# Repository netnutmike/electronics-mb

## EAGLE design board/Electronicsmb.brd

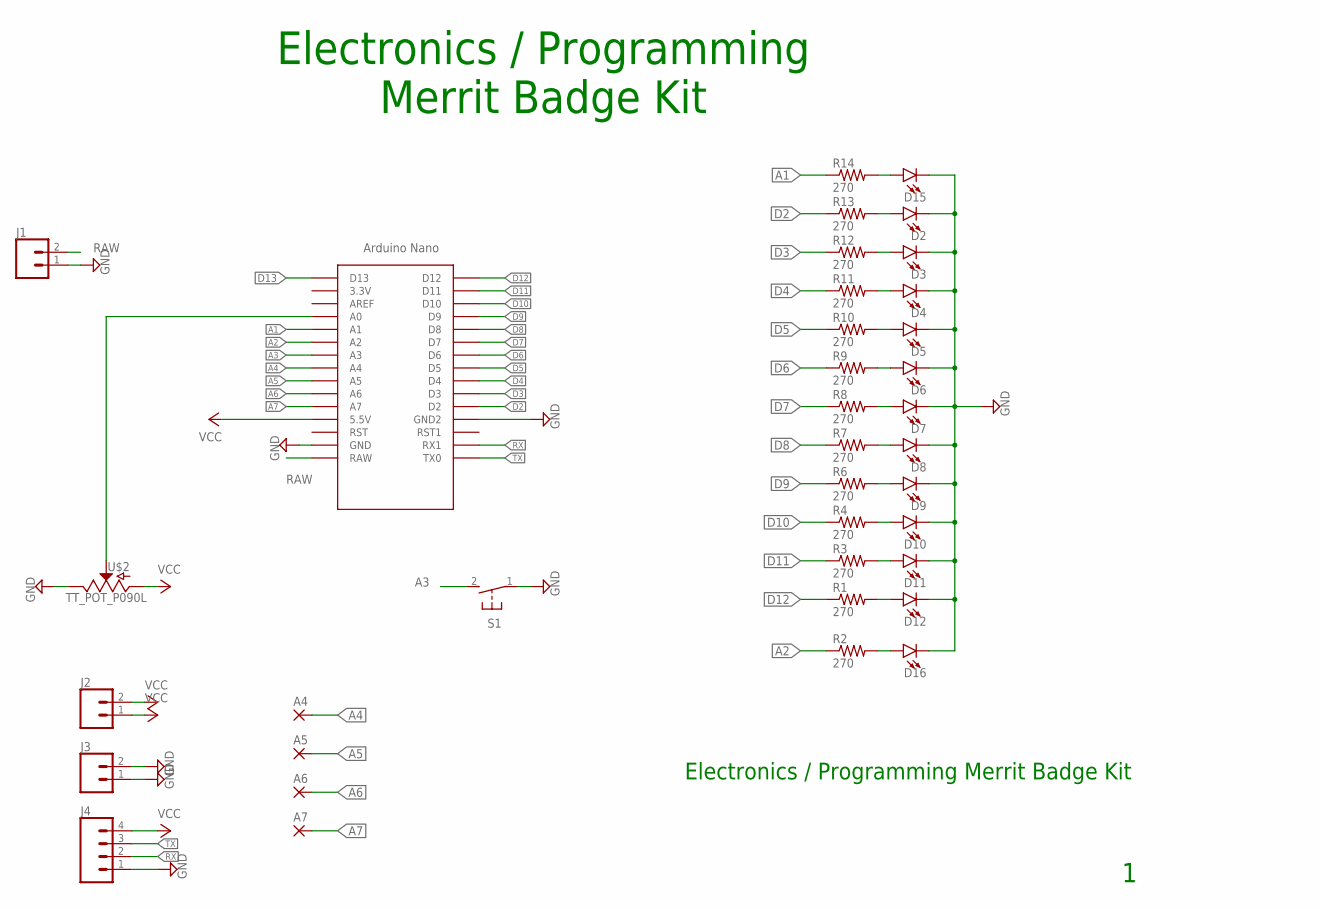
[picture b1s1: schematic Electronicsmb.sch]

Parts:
A4, A5, A6, A7: 2,54/1,0
D2, D3, D4, D5, D6, D7, D8, D9, D10, D11, D12, D15, D16: LED5MM; LED_5MM
J1, J2, J3: CONN_02; 1X02
J4: CONN_04; 1X04
R1, R2, R3, R4, R6, R7, R8, R9, R10, R11, R12, R13, R14: 270; AXIAL-0.4
S1: 31-XX; B3F-31XX
U$1: NANO
U$2: TT_POT_P090L; TT_POT

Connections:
A1: R14.P$1 (1), U$1.A1
A2: R2.P$1 (1), U$1.A2
A3: S1.2 (S), U$1.A3
A4: A4.1, U$1.A4
A5: A5.1, U$1.A5
A6: A6.1, U$1.A6
A7: A7.1, U$1.A7
D2: R13.P$1 (1), U$1.D2
D3: R12.P$1 (1), U$1.D3
D4: R11.P$1 (1), U$1.D4
D5: R10.P$1 (1), U$1.D5
D6: R9.P$1 (1), U$1.D6
D7: R8.P$1 (1), U$1.D7
D8: R7.P$1 (1), U$1.D8
D9: R6.P$1 (1), U$1.D9
D10: R4.P$1 (1), U$1.D10
D11: R3.P$1 (1), U$1.D11
D12: R1.P$1 (1), U$1.D12
D13: U$1.D13
GND: D2.K (C), D3.K (C), D4.K (C), D5.K (C), D6.K (C), D7.K (C), D8.K (C), D9.K (C), D10.K (C), D11.K (C), D12.K (C), D15.K (C), D16.K (C), J1.1, J3.1, J3.2, J4.1, S1.1, U$1.GND, U$1.GND1 (GND2), U$2.P$3 (E)
unnamed: D16.A, R2.P$2 (2)
unnamed: D15.A, R14.P$2 (2)
unnamed: D2.A, R13.P$2 (2)
unnamed: D3.A, R12.P$2 (2)
unnamed: D4.A, R11.P$2 (2)
unnamed: D5.A, R10.P$2 (2)
unnamed: D6.A, R9.P$2 (2)
unnamed: D7.A, R8.P$2 (2)
unnamed: D8.A, R7.P$2 (2)
unnamed: D9.A, R6.P$2 (2)
unnamed: D10.A, R4.P$2 (2)
unnamed: D11.A, R3.P$2 (2)
unnamed: D12.A, R1.P$2 (2)
unnamed: U$1.A0, U$2.P$2 (S)
RAW: J1.2, U$1.RAW
RX: J4.2, U$1.RX1
TX: J4.3, U$1.TX0
VCC: J2.1, J2.2, J4.4, U$1.5V (5.5V), U$2.P$1 (A)

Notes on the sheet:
Electronics / Programming Merrit Badge Kit
Electronics / Programming Merrit Badge Kit

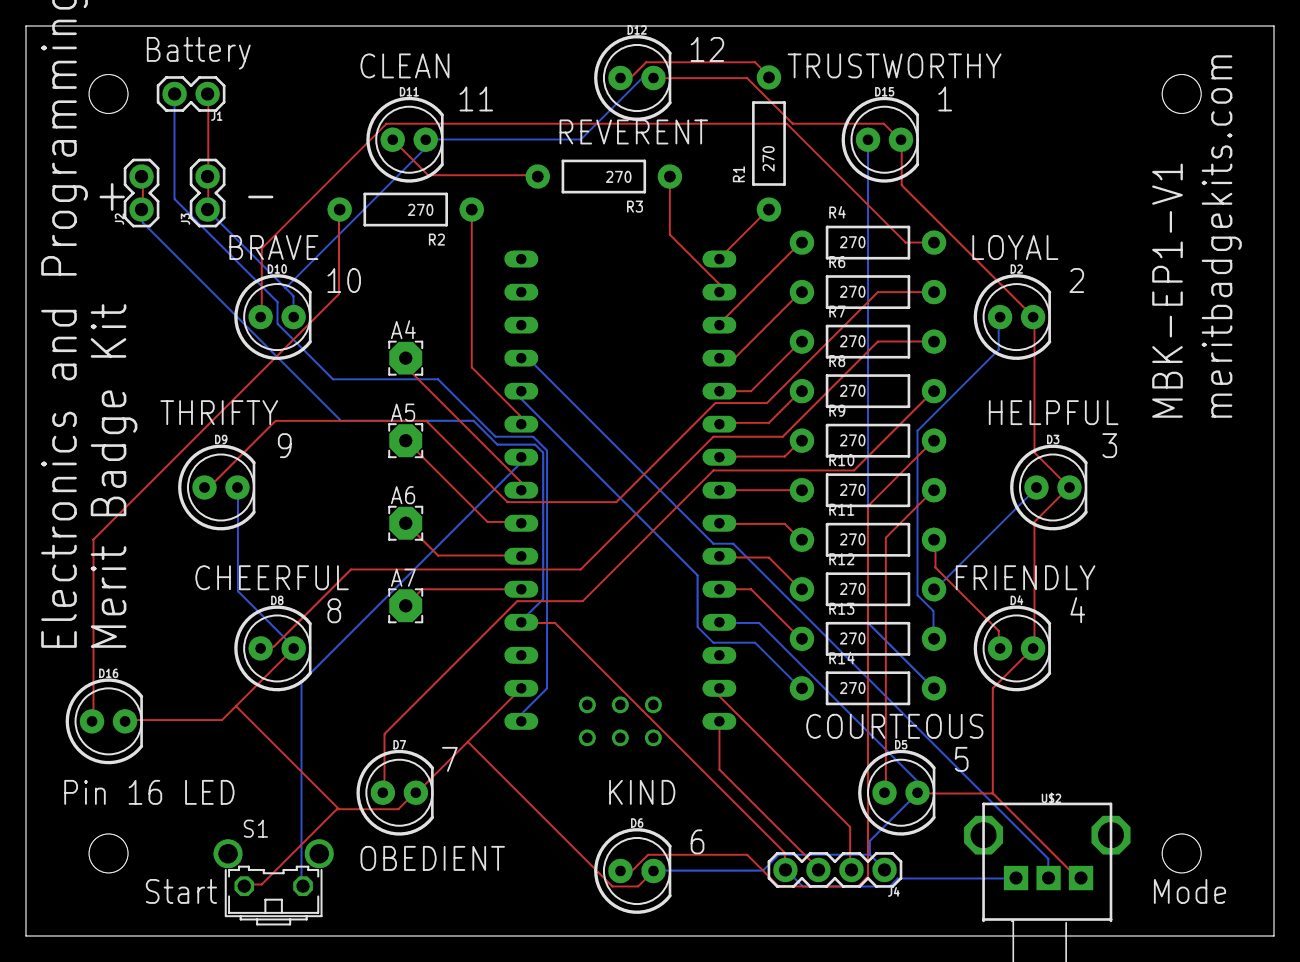
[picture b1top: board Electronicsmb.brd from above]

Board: 2 copper layers, 96.0 x 70.0 mm, 37 parts (0 on the bottom side), 37 nets.

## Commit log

2018-07-12 Cleanup
2018-07-13 board CAM processor ran
2018-07-13 added drill holes
2018-07-13 larger drill holes and points for positive and negative
2018-07-13 minor tweaks
2018-07-22 final tweaks to V1 and starter code
2018-09-28 Added pdf schematic
2018-10-12 Latest Version

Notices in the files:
parts and their libraries:
SparkFun-LED: Licensing: Creative Commons ShareAlike 4.0 International - https://creativecommons.org/licenses/by-sa/4.0
SparkFun: Licensing: CC v3.0 Share-Alike You are welcome to use this library for commercial purposes.
